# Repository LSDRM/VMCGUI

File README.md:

VMCGUI : Versatile Measurement and Control GUI
============
VMCGUI is a PyQt-based Graphical User Interface usable with various measurement and control systems, such as Arduino-based or RaspberryPi-based devices for example, or homemade prototypes. Because developers always reprogram GUIs to plot data of each conceived system, we provide here an interface that can be used with any system, without rewriting the source code. For each system you conceive, you'll have to write a little file containing informations on it, then VMCGUI shall adapt its layer to your needs. The aim of this is to allow acquiring and plotting real-time data from any measurement and control device(s), by a standard computer. This project describes some ways of using the tool, but these have been designed to make it very easy for anyone to program any "kit" in Python for the desired applications. Then, you can build your own system and connect it to a computer where VMCGUI is running, plot your measures from the sensors present in the system, and/or control actuators. The main objective of this project is to give an all-in-one solution while enlarging possibilities with measurement and control prototypes, on experimental benches for example.

> DISCLAIMER : This software is still a prototype and can encouter some bugs, or programming mistakes. I personnaly encourage python-skilled programmers to try giving more proper versions or letting me know about issues that could be fixed.

# [Link to available kits](https://github.com/LSDRM/VMC_Kits)

-----------
Features
-----------

- Adaptative interface to number of sensors and accessible GPIOs.
- Designed to allow very fast sample rate mode.
- Usable without or with any communication protocol from the computer.
- All-in-one solution to correlate control with taken measures.
- Record real-time measurements at sample rate.
- Processing recorded measurements.

-----------
How does it work ?
-----------

You basically have a computer, on which runs VMCGUI. Then, you'll have to connect your system to the computer by the way you prefer, which can be almost every way while the used one can be controlled by a python program. For example, by way I mean :
- USB
- VGA
- WiFi
- Ethernet
- Bluetooth
- Jack
- HDMI
- etc...

The only thing is that you'll have to find a way to control your system by the way you choose, through python, if the way you choose has not been already described in the project resources. This is because, if you create your own measurement and control system, you'll have to write a python file with the instructions to get the measures and/or control the actuators. In short, this python file will make the link between VMCGUI and your system, through the desired communication port. Of course, this project is expected to become a collaborative project, where realised systems can be shared. So you could look at [ready-to-use systems](https://github.com/LSDRM/VMC_Kits) if there is already a project correspond to your needs.

VMCGUI does not really have limits for number of sensors and number of GPIOs, since the GUI shall adapt its layout depending on the given number of sensors and accessible GPIOs in the python program. As you can see below, here is a standard application for VMCGUI, but you can also put external signals on the GPIOs to control VMCGUI and start a record for example. You can also choose another communication port to communicate with an external GPIO board.

Measurement
---------

Your measurements would basically be taken by sensors, with analog or digital outputs. If it's analog, you'll need to use an ADC to convert measures to numerical values, and send it to the computer through the desired protocol/communication port. But you can also use the built-in ADC of the computer's Jack port for example, if you have only one sensor. Then, measurements can be called by the "kit" python program, to get plotted in the VMCGUI.
> You may need to power up your sensor(s). This can be done by a power regulation stage, but care must be taken to ensure that the power supply does not damage the computer port used, if the communication method is not wireless.

Control
---------

Here, the word 'control' refers to controlling external devices, or controlling the VMCGUI. In most cases, control can be done by GPIOs. Those GPIOs can be integrated on the acquisition board, or can be connected to the computer through another communication method on the acquisition board. Controlling external devices could also be done without GPIOs, by interfacing direcly actuators to the computer, through a serial port for example. Because VMCGUI is an all-in-one solution including measurement and control in a single interface, controlling external devices could be done depending on the measurement values.

Speed rates
----------

Ultimately, VMCGUI is intended to being able to plot data with a very high time-resolution, up to the fastest existing devices such as 10 GSPS ADC, which means sampling every 0.1 ns. But, for now, since graphs plotted in VMCGUI are using DateAxisItem from the pyqtgraph package, the maximum resolution is the one of timestamp, which is used in the DateAxisItem package. The timestamp **maximum resolution is about 1 µs**.
Another point is that, when VMCGUI works in a 1-by-1 sample mode, a loop is executed between each sample to plot. This loop is quite long because python is slow to update each graph, and the transfer of data through the communication line can also be slow. To give an order of magnitude, this loop has been measured at about 400 ms between each sample with the first version of the [_DualPressure - Thermocouple_](https://github.com/LSDRM/VMCS/tree/88da0f7f0afaeebaeeff0f13b5e0fb5d95d4da9f/Kits/Personnalized/DualPressure%20-%20Thermocouple) kit, which was working in 1-by-1 sample mode. This kit was using an UART protocol with RS485 standard on a 10 meters long communication line between the computer and the acquisition board, using the following devices and parameters :
- a USB to UART bridge chip (FT231XS) ;
- two RS485 transceivers, at both ends of the line (MAX14840) ;
- a 24 bits ADC with a sample rate of 2000 SPS (ADS122U04) ;
- 3 analog sensors ;
- a 9600 baud rate on communication line ;
- for a total of 102 bytes exchanged per loop between the computer and the acquisition board, neglecting the usage of GPIOs integrated to the ADC.

Then, we can calculate that the data exchange on the line contribute for $102\times 8\times 1/9600 = 85\ ms$ per loop theorically. This means that the approximative remaining of ca. 315 ms is due to the execution of pythons instructions. So the lever to improve the speed rate of the system, is to minimize the number of python instructions updating the sampling. To perform this, we can consider acquiring multiple samples in a row without asking for each sample, and instead asking for a quantity N of samples. Then, the plot(s) in VMCGUI shall update by groups of N samples, each separated by the used analog-to-digital conversion rate. In the figure below, I provide an example of an UART frame from the computer in N-by-N mode (using a USB to UART bridge or other), asking for N samples to the acquisition board. Because there is more than 1 sensor on the acquisition board, the ADC will need to switch from the first to the second sensor. This is usually performed by rewriting a register in the ADC, which needs to send another frame to the ADC. Because we don't want to send too much frame from the VMCGUI (which is python-based and slow), we may use a microcontroller between the computer and the ADC, in charge of sending frames from the switching sensors. In this configuration, the microcontroller must be preprogrammed to understand what it has to do when receiving the frames containing the number N. The preprogramming can be performed on starting VMCGUI in the "kit" python file, or outside VMCGUI using another software (e.g. Arduino IDE for an Arduino-based acquisition board). The used microcontroller can either store all N samples before sending them, or immediatly send each sample after acquisition.

----------
Recording measurements and data processing
----------

VMCGUI provides a recording solution to store your measurements in files. Once recorded, you can reopen and plot your datas to generate SVG, matplotlib, CSV,... files and graphs.
> Math operations on plots and between plots in the "Load Data" window are also possible but still under debugging.

----------
Some examples of use
----------

#### Using an Arduino
The configuration that may be the most used with VMCGUI is probably using an Arduino connected to the computer through USB. This configuration is probably the most simple to set up, because it doesn't need complex development of special data acquisition board. You only need to connect your sensors and actuators to the Arduino as suggested in the documentation of the sensors/actuators, or in the Arduino's documentation if it exists. Then, you'll need to talk to the Arduino through python commands, in the "kit" python file of VMCGUI. This can be performed in a very simple way with the _pyfirmata_ library (see https://realpython.com/arduino-python/).

#### Customized acquisition board over long distances
Since VMCGUI has been firstly developed for long distance (about 10 meters) applications and highly noisy environment, the main configuration that has been studied is the following one, using UART communication protocol through RS485 or RS422 standards. This configuration enables one to embed the acquisition board on a system with difficult accessibility, through wire connections. The "Data Acquisition IC" could be a microcontroller with ADC, or directly an ADC that has UART communication protocol (e.g. ADS122U04 which include GPIOs).
> Note that in the latter case, with direct connection to an UART ADC, you will not be able to have very fast sample rate with more than one sensor. This is because an ADC generally needs to receive commands to switch its conversion channels between sensors. Then, the N-by-N mode is not possible in this exact configuration.

#### Wireless acquisition board
The previous configuration shows one way of integrating the frame grabber on long-distance or hard-to-reach systems. This configuration enables the acquisition board to be integrated into systems with a wireless connection to the computer. Setting up such a configuration may be a little trickier, but remains a possibility for your system if wireless connection is essential.

-----------
Install
-----------

First of all, make sure you already have installed Python 3.8 at least on your computer. No elaborate compatibility tests have been performed for different python versions with the interface, but I recommend to use versions not too far from the ones given in the next section.

Clone this repository (check the [tutorial](https://docs.github.com/articles/cloning-a-repository) if you don't know how to do) on your computer at the desired path, then run `pip install -r "C:\...\VMCGUI\APP\requirements.txt"` in the command prompt. Don't forget to replace `C:\...\` by the path where you cloned the current repository.
> The previous path is given under Windows format, so be sure of using the correct path format if you are not working under Windows.

Now, you can navigate to the app directory using `cd VMCGUI/APP`, then run the interface using python with the following command : `python VMCGUI.py`

----------
Configuring new kits
----------

Kits available from the start dialog of VMCGUI are loaded from the Python files available in the [`APP/Kits`](APP/Kits) folder. To configure a new kit for your application, you need to use the [`#BlankKit.py`](APP/Kits/#BlankKit.py) template from the [`APP/Kits`](APP/Kits) folder.
> Note that placing a `#` at the begining of a kit file name will ignore it in the start dialog.

If you want to check for existing kits, you may check at [the repo of available kits](https://github.com/LSDRM/VMC_Kits).

----------
Compatibility
----------

For now, VMCGUI has been developped under Windows 10, and has not been tested on Mac and Linux. The app is given as Python source code, so needs Python and few libraries to be installed. VMCGUI is reported to works fine with versions :
- Python 3.11.3
- pyqtgraph 0.13.3
- numpy 1.24.3
- scipy 1.10.1
- PyQt5 5.15.9
- PyQtWebEngine 5.15.6

----------
Next steps
----------

- [ ] Create documentation : [Work in progress](https://github.com/LSDRM/VMCGUI/tree/dev-docs)
- [ ] Fix Windows 11 bug with ftd2xx.dll
- [ ] Move to pyftdi Python library instead of ftd2xx

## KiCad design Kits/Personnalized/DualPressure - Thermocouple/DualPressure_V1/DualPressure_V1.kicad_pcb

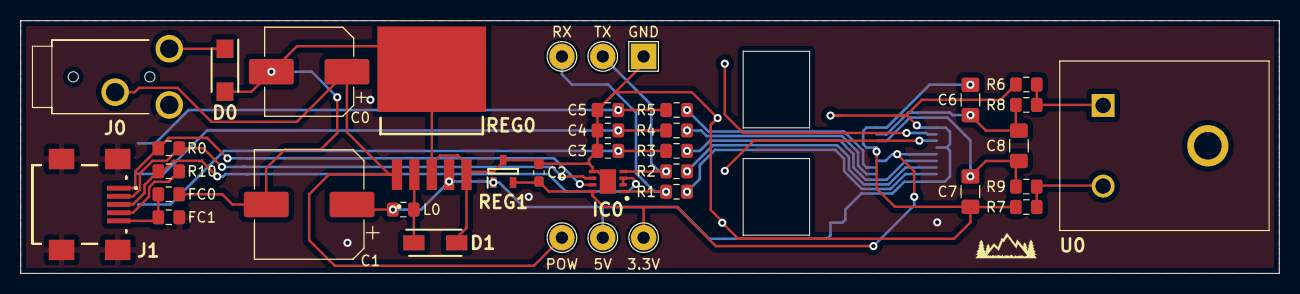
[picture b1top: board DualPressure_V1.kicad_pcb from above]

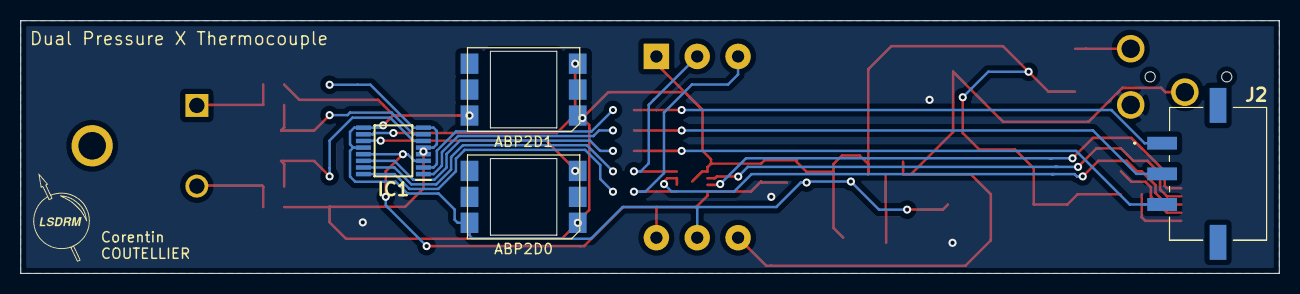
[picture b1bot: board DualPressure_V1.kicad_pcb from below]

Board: 2 copper layers, 123.2 x 24.8 mm, 41 parts (4 on the bottom side), 28 nets.

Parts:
3.3V, 5V: TestPoint; TestPoint_THTPad_D2.5mm_Drill1.2mm
ABP2D0, ABP2D1: ABP2D
C0: 100u; CP_Elec_8x10.5
C1: 1000u; CP_Elec_10x10.5
C2: 1u; C_0603_1608Metric_Pad1.05x0.95mm_HandSolder
C3: FREECHOICE; C_0805_2012Metric_Pad1.15x1.40mm_HandSolder
C4, C5: FC; C_0805_2012Metric_Pad1.15x1.40mm_HandSolder
C6, C7: 10n; C_1206_3216Metric_Pad1.42x1.75mm_HandSolder
C8: 10u; C_1206_3216Metric_Pad1.42x1.75mm_HandSolder
D0: SBRT3U60SAF-13; SODFL5226X110N
D1: SK34A; DIOM5126X230N
FC0, FC1: R; R_0805_2012Metric_Pad1.15x1.40mm_HandSolder
GND: TestPoint; TestPoint_THTPad_2.5x2.5mm_Drill1.2mm
IC0: MAX14840EATA+; SON65P300X300X80-9N
IC1: ADS122U04IPW; SOP65P640X120-16N
J0: STX-3000; STX3000
J1: USB2066-05-RBHM-15-STB-00-00-A; USB206605RBHM15STB0000A
J2: 2-1445057-3; 214450573
L0: 100u; L_0805_2012Metric_Pad1.15x1.40mm_HandSolder
POW: TestPoint; TestPoint_THTPad_D2.5mm_Drill1.2mm
R0, R10: 120; R_0805_2012Metric_Pad1.15x1.40mm_HandSolder
R1, R2, R3, R4, R5: 47; R_0805_2012Metric_Pad1.15x1.40mm_HandSolder
R6, R7: 1M; R_0805_2012Metric_Pad1.15x1.40mm_HandSolder
R8, R9: 1k; R_0805_2012Metric_Pad1.15x1.40mm_HandSolder
REG0: LM2576D2TR4-5G; D2TSUFFIX-CASE936A-02-ISSUEC
REG1: AP7333-33SAG-7; SOT96P240X135-3N
RX: TestPoint; TestPoint_THTPad_D2.5mm_Drill1.2mm
TX: TestPoint; TestPoint_THTPad_D2.5mm_Drill1.2mm
U0: AM-K-PCB; AMKPCB

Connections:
/3.3V: 3.3V.1, C2.1, IC0.8, IC1.3, IC1.13, REG1.2
/5V: 5V.1, ABP2D0.6, ABP2D1.6, C1.1, IC1.9, IC1.12, L0.1, R6.1, REG0.4, REG1.1
/#ENABLE: IC0.2, IC0.3, J1.3, R10.1
/AIN0: ABP2D0.3, IC1.11
/AIN1: ABP2D1.3, IC1.10
/AIN2: C6.2, C8.1, IC1.7, R8.1
/AIN3: C7.1, C8.2, IC1.6, R9.1
/ENABLE: J1.4, R10.2
/GPIO0: C5.1, J2.1, R5.2
/GPIO1: C4.1, J2.2, R4.2
/GPIO2: C3.1, J2.3, R3.1
/POWER: C0.1, J0.1, POW.1, REG0.1
/SHIELD: FC1.2, J0.3, J1.MP1, J1.MP2, J1.MP3, J1.MP4
GND: ABP2D0.1, ABP2D1.1, C0.2, C1.2, C2.2, C3.2, C4.2, C5.2, C6.1, C7.2, D0.2, D1.2, FC0.2, GND.1, IC0.5, IC0.9, IC1.4, IC1.5, IC1.8, R7.2, REG0.3, REG0.5, REG0.6, REG1.3
unnamed: D0.1, J0.2
unnamed: D1.1, L0.2, REG0.2
unnamed: FC0.1, FC1.1, J1.5
unnamed: IC0.1, R1.1, RX.1
unnamed: IC0.4, R2.1, TX.1
unnamed: IC0.6, J1.2, R0.2
unnamed: IC0.7, J1.1, R0.1
unnamed: IC1.1, R4.1
unnamed: IC1.2, R5.1
unnamed: IC1.14, R3.2
unnamed: IC1.15, R2.2
unnamed: IC1.16, R1.2
unnamed: R6.2, R8.2, U0.1
unnamed: R7.1, R9.2, U0.2

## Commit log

2023-12-01 Rename Setup.md to README_Setup.md
2023-12-01 Rename AddingKits.md to README.md
2023-12-01 Rename README_Setup.md to README.md
2023-12-07 Rename README.md to README.md
2024-01-05 Updated full repository
2024-01-23 Updated files
2024-01-23 Remove unecessary files
2026-06-23 Initialized documentation
2026-06-24 Add .gitignore to libsForKits folder
2026-06-24 Add and setup .gitignore files
2026-06-24 Update Kits .gitignore file
2026-06-24 Add .gitignore files
2026-06-24 Remove files
2026-06-24 Update .gitignore file
2026-06-24 Add .gitignore to ignore __pycache__ directory
2026-06-24 Update .gitignore to ignore __pycache__
    Added rule to ignore __pycache__ directory.
2026-06-24 Add .gitignore to ignore __pycache__
    Add .gitignore to exclude __pycache__ directory
2026-06-24 Update docs
2026-06-24 Add next steps section to README
    Added next steps section with tasks for documentation and bug fixes.
